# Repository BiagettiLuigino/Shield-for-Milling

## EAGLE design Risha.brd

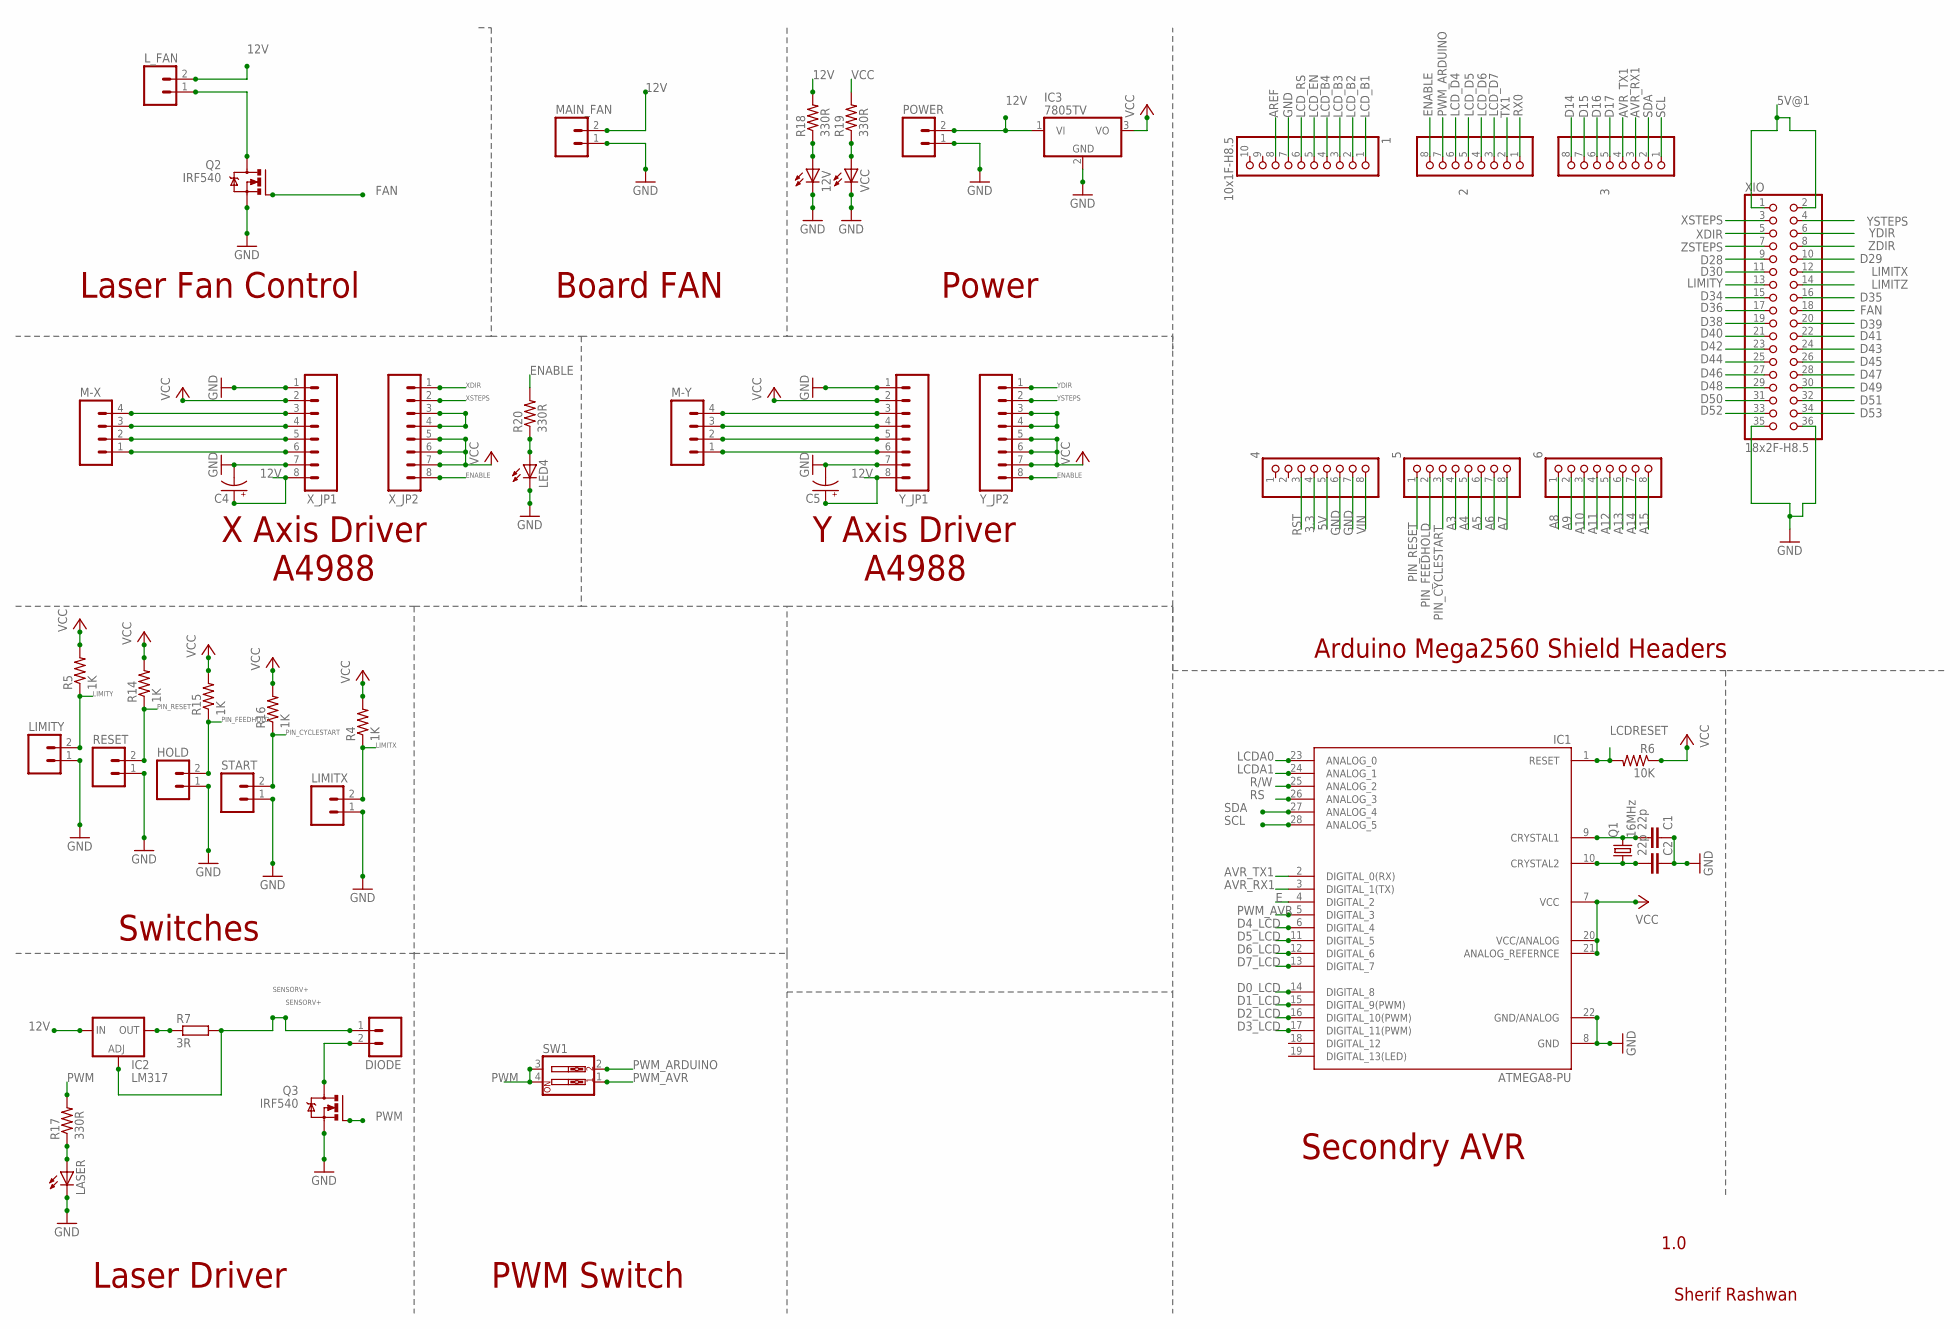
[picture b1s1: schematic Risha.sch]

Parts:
1: 10x1F-H8.5; 1X10
2, 3, 4, 5, 6: 8x1F-H8.5; 1X08
12V: LED3MM
C1, C2: 22p; C2.5-2
C4, C5: CAP_POLPTH2; CPOL-RADIAL-10UF-25V
DIODE: M02PTH; 1X02
HOLD: M02PTH; 1X02
IC1: ATMEGA8-PU; DIL28-3
IC2: LM317; TO3-K02
IC3: 7805TV; TO220V
LASER: LED3MM
LED4: LED3MM
LIMITX: M02PTH; 1X02
LIMITY: M02PTH; 1X02
L_FAN: M02PTH; 1X02
M-X: M04PTH; 1X04
M-Y: M04PTH; 1X04
MAIN_FAN: M02PTH; 1X02
POWER: M02PTH; 1X02
Q1: 16MHz; HC49US
Q2, Q3: IRF540; TO220BV
R4, R5, R14, R15, R16: 1K; 1/6W-RES
R6: 10K; 1/6W-RES
R7: 3R; 0309/12
R17, R18, R19, R20: 330R; 1/6W-RES
RESET: M02PTH; 1X02
START: M02PTH; 1X02
SW1: SW_DIP-2; EDG-02
VCC: LED3MM
XIO: 18x2F-H8.5; 2X18
X_JP1, X_JP2: M08; 1X08
Y_JP1, Y_JP2: M08; 1X08

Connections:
3.3: 4.4
5V: 4.5
5V@1: XIO.1, XIO.2
12V: C4.1 (+), C5.1 (+), IC2.1 (IN), IC3.1 (VI), L_FAN.2, MAIN_FAN.2, POWER.2, R18.2, X_JP1.8, Y_JP1.8
A3: 5.4
A4: 5.5
A5: 5.6
A6: 5.7
A7: 5.8
A8: 6.1
A9: 6.2
A10: 6.3
A11: 6.4
A12: 6.5
A13: 6.6
A14: 6.7
A15: 6.8
AREF: 1.8
AVR_RX1: 3.3, IC1.3 (DIGITAL_1(TX))
AVR_TX1: 3.4, IC1.2 (DIGITAL_0(RX))
D0_LCD: IC1.14 (DIGITAL_8)
D1_LCD: IC1.15 (DIGITAL_9(PWM))
D2_LCD: IC1.16 (DIGITAL_10(PWM))
D3_LCD: IC1.17 (DIGITAL_11(PWM))
D4_LCD: IC1.6 (DIGITAL_4)
D5_LCD: IC1.11 (DIGITAL_5)
D6_LCD: IC1.12 (DIGITAL_6)
D7_LCD: IC1.13 (DIGITAL_7)
D14: 3.8
D15: 3.7
D16: 3.6
D17: 3.5
D28: XIO.9
D29: XIO.10
D30: XIO.11
D34: XIO.15
D35: XIO.16
D36: XIO.17
D38: XIO.19
D39: XIO.20
D40: XIO.21
D41: XIO.22
D42: XIO.23
D43: XIO.24
D44: XIO.25
D45: XIO.26
D46: XIO.27
D47: XIO.28
D48: XIO.29
D49: XIO.30
D50: XIO.31
D51: XIO.32
D52: XIO.33
D53: XIO.34
E: IC1.4 (DIGITAL_2)
ENABLE: 2.8, R20.2, X_JP2.8, Y_JP2.8
FAN: Q2.G, XIO.18
GND: 1.7, 4.6, 4.7, 12V.K (C), C1.1, C2.1, C4.2 (-), C5.2 (-), HOLD.1, IC1.8 (GND), IC1.22 (GND/ANALOG), IC3.2 (GND), LASER.K (C), LED4.K (C), LIMITX.1, LIMITY.1, MAIN_FAN.1, POWER.1, Q2.S, Q3.S, RESET.1, START.1, VCC.K (C), XIO.35, XIO.36, X_JP1.1, X_JP1.7, Y_JP1.1, Y_JP1.7
LCDA0: IC1.23 (ANALOG_0)
LCDA1: IC1.24 (ANALOG_1)
LCDRESET: IC1.1 (RESET), R6.2
LCD_B1: 1.1
LCD_B2: 1.2
LCD_B3: 1.3
LCD_B4: 1.4
LCD_D4: 2.6
LCD_D5: 2.5
LCD_D6: 2.4
LCD_D7: 2.3
LCD_EN: 1.5
LCD_RS: 1.6
LIMITX: LIMITX.2, R4.1, XIO.12
LIMITY: LIMITY.2, R5.1, XIO.13
LIMITZ: XIO.14
unnamed: L_FAN.1, Q2.D
unnamed: M-Y.4, Y_JP1.3
unnamed: M-Y.3, Y_JP1.4
unnamed: M-Y.2, Y_JP1.5
unnamed: M-Y.1, Y_JP1.6
unnamed: Y_JP2.3, Y_JP2.4
unnamed: C1.2, IC1.9 (CRYSTAL1), Q1.2
unnamed: C2.2, IC1.10 (CRYSTAL2), Q1.1
unnamed: LASER.A, R17.1
unnamed: IC2.3 (OUT), R7.1
unnamed: DIODE.2, Q3.D
unnamed: 12V.A, R18.1
unnamed: R19.1, VCC.A
unnamed: LED4.A, R20.1
unnamed: M-X.4, X_JP1.3
unnamed: M-X.3, X_JP1.4
unnamed: M-X.2, X_JP1.5
unnamed: M-X.1, X_JP1.6
unnamed: X_JP2.3, X_JP2.4
PIN_CYCLESTART: 5.3, R16.1, START.2
PIN_FEEDHOLD: 5.2, HOLD.2, R15.1
PIN_RESET: 5.1, R14.1, RESET.2
PWM: Q3.G, R17.2, SW1.3, SW1.4
PWM_ARDUINO: 2.7, SW1.2
PWM_AVR: IC1.5 (DIGITAL_3), SW1.1
R/W: IC1.25 (ANALOG_2)
RS: IC1.26 (ANALOG_3)
RST: 4.3
RX0: 2.1
SCL: 3.1, IC1.28 (ANALOG_5)
SDA: 3.2, IC1.27 (ANALOG_4)
SENSORV+: DIODE.1, IC2.2 (ADJ), R7.2
TX1: 2.2
VCC: IC1.7 (VCC), IC1.20 (VCC/ANALOG), IC1.21 (ANALOG_REFERNCE), IC3.3 (VO), R4.2, R5.2, R6.1, R14.2, R15.2, R16.2, R19.2, X_JP1.2, X_JP2.5, X_JP2.6, X_JP2.7, Y_JP1.2, Y_JP2.5, Y_JP2.6, Y_JP2.7
VIN: 4.8
XDIR: XIO.5, X_JP2.1
XSTEPS: XIO.3, X_JP2.2
YDIR: XIO.6, Y_JP2.1
YSTEPS: XIO.4, Y_JP2.2
ZDIR: XIO.8
ZSTEPS: XIO.7

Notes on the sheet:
Arduino Mega2560 Shield Headers
1.0
Sherif Rashwan
X Axis Driver
A4988
Power
Laser Fan Control
Board FAN
Switches
Y Axis Driver
Secondry AVR
Laser Driver
PWM Switch

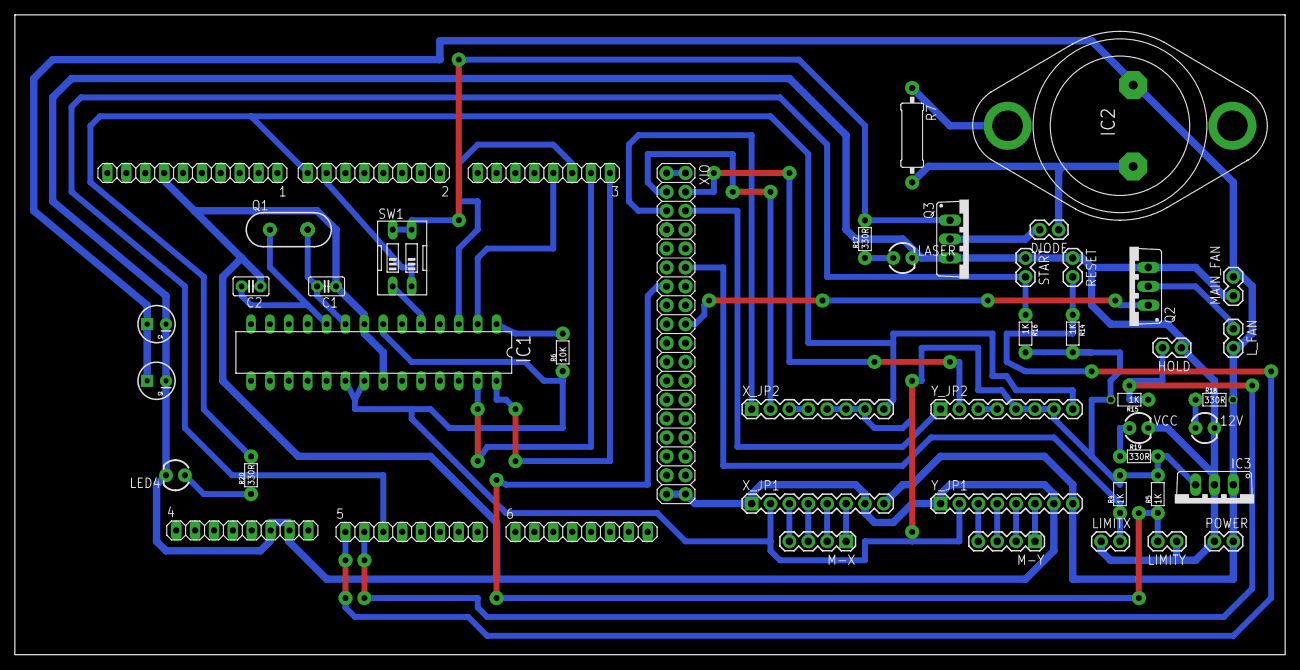
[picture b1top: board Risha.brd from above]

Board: 2 copper layers, 170.8 x 86.0 mm, 48 parts (0 on the bottom side), 43 nets.

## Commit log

2014-10-15 :neckbeard: Added .gitattributes & .gitignore files
2014-10-15 Risha Shield for Milling
